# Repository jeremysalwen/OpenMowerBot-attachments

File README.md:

# OpenMower Discord History — Attachments

Binary attachments for the [OpenMowerBot](https://github.com/jeremysalwen/OpenMowerBot)
Discord history corpus. This repository holds the files themselves; the searchable
message corpus and the CLI live in the main repository.

## Why this is a separate repository

Attachments are large (hundreds of MB) and write-once. Keeping them here means:

- `git clone` of the main repository stays small and never downloads image data.
- The files are stored as ordinary Git objects, **not** Git LFS, so they are not
  subject to an LFS bandwidth budget.
- The static archive on GitHub Pages hotlinks them directly from
  `raw.githubusercontent.com`, so images render without bundling them into the
  1 GB Pages site limit.

## Layout

Files are stored as `<channelId>/<messageId>-<fileName>`, matching the
`localPath` suffix recorded in the main corpus (`data/attachments/` prefix removed).

The raw URL for an attachment is:

```
https://raw.githubusercontent.com/jeremysalwen/OpenMowerBot-attachments/main/<channelId>/<messageId>-<fileName>
```

## Do not use Git LFS here

This repository must stay on plain Git objects. Adding LFS tracking would
reintroduce the bandwidth budget that made attachments unusable in the main repo.

## MISSING.tsv

`MISSING.tsv` lists attachments that are referenced by the corpus but are not in
this repository. Their Discord CDN URLs have expired, and the only remaining
copies are Git LFS objects in the main repository, which are currently behind an
exhausted LFS budget. See the main repository's README for how to recover them.

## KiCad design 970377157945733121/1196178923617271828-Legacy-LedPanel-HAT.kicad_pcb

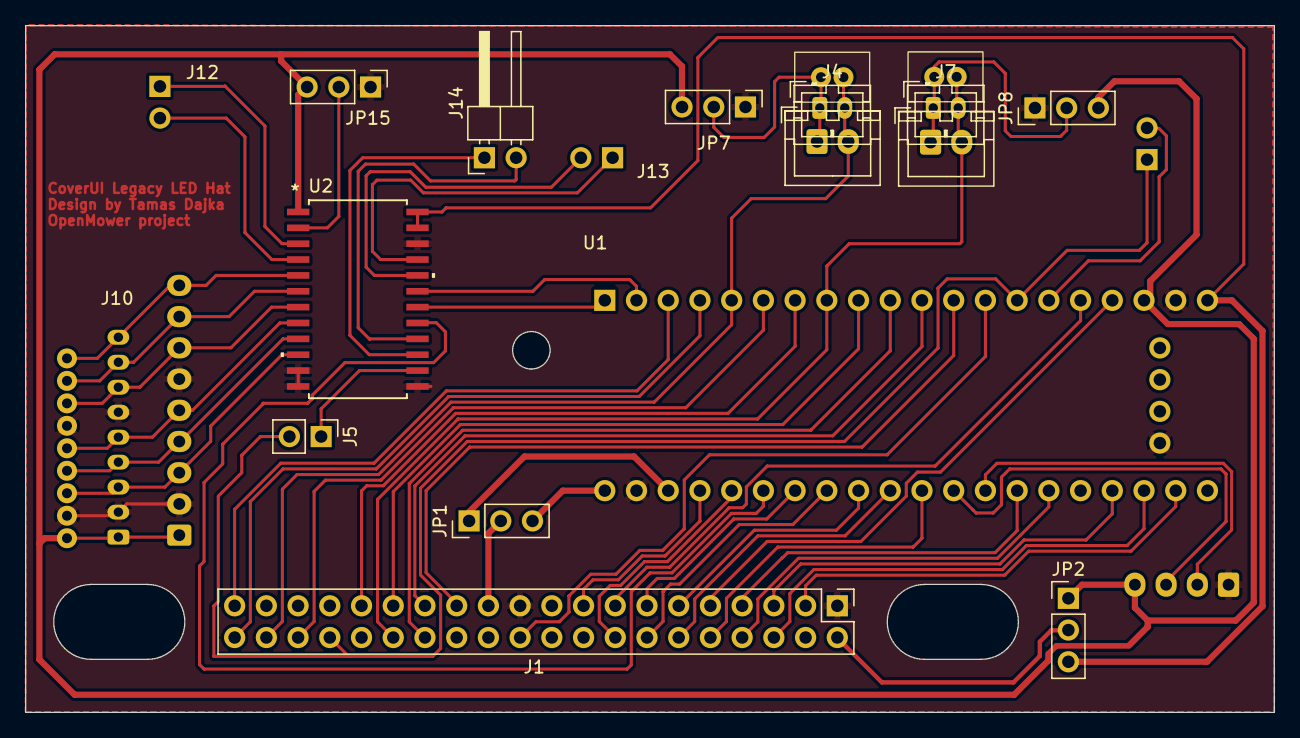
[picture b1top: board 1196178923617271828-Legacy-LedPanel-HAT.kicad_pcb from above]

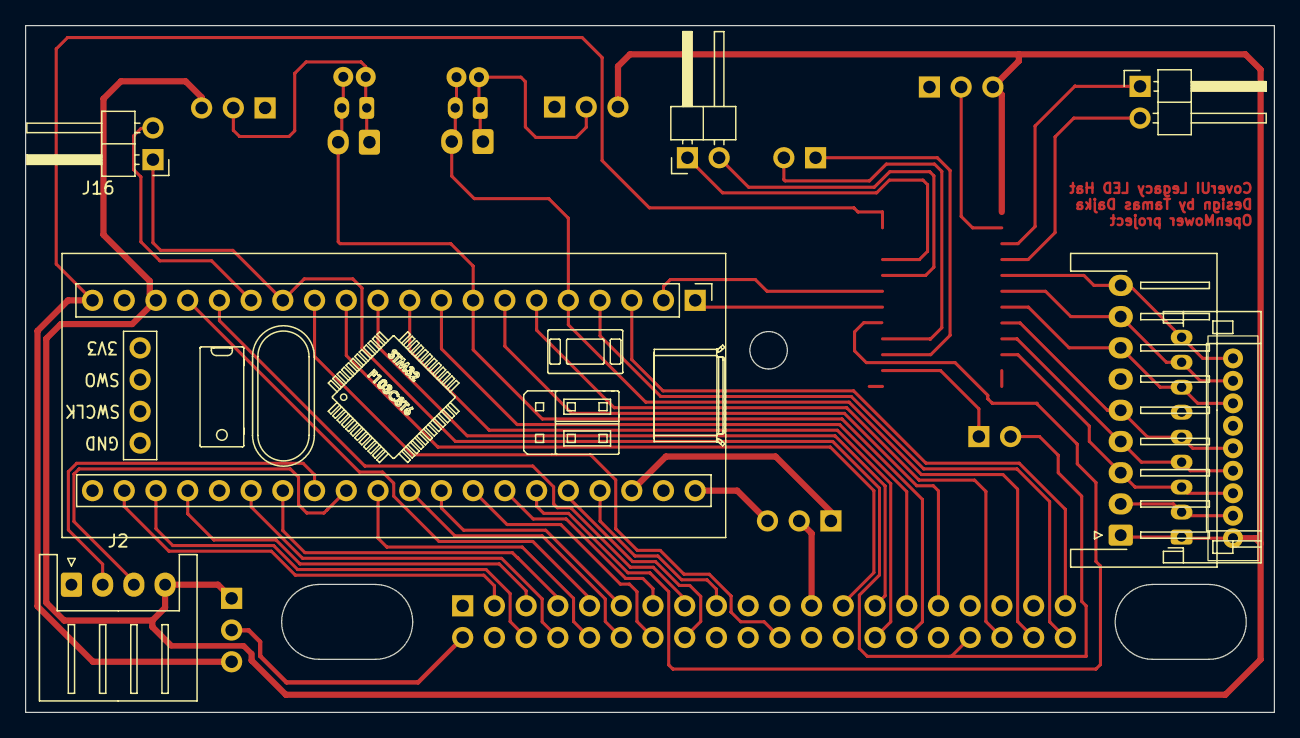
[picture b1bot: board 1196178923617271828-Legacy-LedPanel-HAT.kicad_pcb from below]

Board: 2 copper layers, 100.0 x 55.0 mm, 23 parts (8 on the bottom side), 53 nets.

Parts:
J1: Conn_02x20_Odd_Even; PinHeader_2x20_P2.54mm_Vertical
J2: OM_Serial; JST_XH_S4B-XH-A_1x04_P2.50mm_Horizontal
J3, J8: 1.8mm; conn_01x2_1.8mm
J4, J7: 2mm; JST_PH_B2B-PH-K_1x02_P2.00mm_Vertical
J5: SOUT_to_STM32; PinHeader_1x02_P2.54mm_Vertical
J5_STOP1, J6_STOP2: 2.54mm; JST_XH_B2B-XH-A_1x02_P2.50mm_Vertical
J9: 1.8mm; conn_01x9_1.8mm
J10: 2mm; JST_PH_S9B-PH-K_1x09_P2.00mm_Horizontal
J11: 2.54mm; JST_XH_S9B-XH-A-1_1x09_P2.50mm_Horizontal
J12: Spare LevelShift A0_A1; PinHeader_1x02_P2.54mm_Horizontal
J13: Spare LS OUT B0_B1; PinHeader_1x02_P2.54mm_Horizontal
J14: LS OUT S1_S2; PinHeader_1x02_P2.54mm_Horizontal
J16: I2C; PinHeader_1x02_P2.54mm_Horizontal
JP1, JP2: CoverUI 5V or 3V3; PinHeader_1x03_P2.54mm_Vertical
JP7: STOP1 GND_or_5V; PinHeader_1x03_P2.54mm_Vertical
JP8: STOP2 GND_or_5V; PinHeader_1x03_P2.54mm_Vertical
JP15: LS GND_or_5V; PinHeader_1x03_P2.54mm_Vertical
U1: STM32F401RC blue pill; YAAJ_BluePill_SWD_1
U2: Hall Level-shifter 74LVC4245AD; SOT137-1_NEX

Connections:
+5V: J2.4, J9.1, J10.1, J11.1, JP1.3 (B), JP2.1 (A), JP7.3 (B), JP8.3 (B), JP15.3 (B), U1.18 (5V), U1.40 (5V), U2.1 (VCCA)
/ESTOP1: U1.1 (PB12), U2.18 (B3)
/ESTOP1_5V: J9.8, J10.8, J11.8, U2.6 (A3)
/ESTOP2: U1.2 (PB13), U2.19 (B2)
/ESTOP2_5V: J9.9, J10.9, J11.9, U2.5 (A2)
/JP1-1 Right Bumper: J1.39, U1.3 (PB14)
/JP1-4 Lift: J1.40, U1.4 (PB15)
/JP1-7 Left Bumper: J1.36, U1.6 (PA9)
/JP1-10 LiftX: J1.34, J5.2, J16.1, U1.14 (PB6)
/JP5-2 STOP1: J1.30, J6_STOP2.2, J7.2, J8.2, U1.8 (PA11)
/JP6-2 STOP2: J1.38, J3.2, J4.2, J5_STOP1.2, U1.5 (PA8)
/LED1 - D1: J1.3, U1.22 (PC13)
/LED2 - D2: J1.5, U1.24 (PC15)
/LED3 - D3: J1.6, U1.23 (PC14)
/LED4 - D4: J1.7, U1.27 (PA1)
/LED5 - D5: J1.8, U1.26 (PA0)
/LED6 - D6: J1.10, U1.30 (PA4)
/LED7 - D7: J1.12, U1.31 (PA5)
/LED8 - D8: J1.14, U1.33 (PA7)
/LED9 - D9: J1.16, U1.36 (PB2)
/LED10 - D10: J1.15, U1.16 (PB8)
/LED11 - D11: J1.17, U1.37 (PB10)
/Pico-RX_STM32-TX: J2.2, U1.28 (PA2)
/Pico-TX_STM32-RX: J2.3, U1.29 (PA3)
/RAIN: U1.35 (PB1), U2.17 (B4)
/RAIN_5V: J9.7, J10.7, J11.7, U2.7 (A4)
/S1 (button): J1.22, U1.13 (PB5)
/S1_5V: J9.4, J10.4, J11.4, U2.9 (A6)
/S1_LS: J14.1, U2.15 (B6)
/S2 (button): J1.9, U1.17 (PB9)
/S2_5V: J9.5, J10.5, J11.5, U2.8 (A5)
/S2_LS: J14.2, U2.16 (B5)
/S3 (button): J1.11, U1.32 (PA6)
/S4 (button): J1.29, U1.9 (PA12)
/S5 (button): J1.13, U1.34 (PB0)
/S6 (button): J1.31, U1.7 (PA10)
/S7 (button): J1.25, U1.12 (PB4)
/S8 (button): J1.28, U1.10 (PA15)
/S9 (button): J1.27, U1.11 (PB3)
/SDA1: J16.2, U1.15 (PB7)
/SOUT_5V: J9.3, J10.3, J11.3, U2.10 (A7)
/SOUT_LS: J5.1, U2.14 (B7)
/VCC: J1.2, J1.23, JP1.2 (C), JP2.2 (C)
GND: J1.1, J1.21, J2.1, J9.2, J9.6, J10.2, J10.6, J11.2, J11.6, JP7.1 (A), JP8.1 (A), JP15.1 (A), U1.19 (GND), U1.39 (GND), U1.41 (GND), U2.11 (GND), U2.12 (GND), U2.13 (GND), U2.22 (OE*)
unnamed: J3.1, J4.1, J5_STOP1.1, JP7.2 (C)
unnamed: J6_STOP2.1, J7.1, J8.1, JP8.2 (C)
unnamed: J12.1, U2.3 (A0)
unnamed: J12.2, U2.4 (A1)
unnamed: J13.1, U2.21 (B0)
unnamed: J13.2, U2.20 (B1)
unnamed: JP1.1 (A), U1.38 (3V3)
unnamed: JP2.3 (B), U1.20 (3V3), U2.23 (VCCB), U2.24 (VCCB)
unnamed: JP15.2 (C), U2.2 (DIR)
